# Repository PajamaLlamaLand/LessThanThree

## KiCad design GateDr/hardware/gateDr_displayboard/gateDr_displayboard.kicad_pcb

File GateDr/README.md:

# Gate Dr. 

The Gate Doctor is a multi-functional logic, comparator, and gate manipulation module in the Eurorack synth format.

The module is based around extracting, combining, and further modulating gate signals from your Eurorack system. It can be a simple comparator, logic module, clock divider, probability generator, gate delay (plus plenty of other features/modulation options), or many combinations of those at once!

The module consists of 2 channels, each with 2 inputs and 2 outputs, and 2 global CV inputs that can be routed to almost any parameter in the module. Each input is fed into a comparator with adjustable threshold (or assign it to CV)- each pair of channel inputs are then fed to 2 different logic gates (including a 'Bypass' that will send the comparator result to the Output section below it). The results of the logic operations are then fed into the Output section where the signal can be fed through a variety of gate-centric utilities, such as a clock divider, probability mask, gate delay, and more. 

As you can probably see already (and please read the manual in /GateDr/documentation/ to see all the other features it has!), the Gate Dr. is a very flexible utility tool designed to be able to create, combine, and fine-tune gate signals to send out to the rest of your Eurorack system. Whether you are extracting gates from LFOs, combining multiple gate sequencers and probability to create new generative sequences, or simply trimming a gate signal's length to make it play well with a module that wants short triggers, you may not need every feature it has on a given patch but it can find a place in nearly every patch you make <3

The Gate Doctor is currently [available for sale here.](https://www.tindie.com/products/41107/)

NOTE: The Gate Dr. is designed for control signals, not audio rate signals. However, you are highly encouraged to abuse this fact to create some unique glitchy digital textures.

# Feature List

Each channel in the Gate Dr. contains:

>   2 comparators with adjustable threshold, hysteresis, and ability to invert the signal.

>   2 separate logical operations on the 2 inputs, including combinational logic (AND, NAND, OR, NOR, XOR, XNOR), sequential logic (S-R latch, D-latch), and a BYPASS operation which ignores the 'operation' processing.

>   Output processing blocks that include various gate-related utilities, including a clock divider, a gate start-delay, a probability control, and a robust gate-to-trigger converter.

>   2 globally assignable CV signals, with CV control available for the vast majority of parameters.

The Gate Dr. also has the following features:

>   OLED screen, pushbutton encoder, and two Channel buttons for easy access to any parameter. 

>   Simple, easy to understand menu interface with shortcuts to menus on the panel. 

>   Automatic saving of all settings parameters. 

>   Reverse power protection. 

>   Super slim skiff-friendly design. 

>   USB-Micro Type B connection for easy drag-and-drop firmware updates. 

## Repo info

This repository contains the hardware design files and firmware for the Gate Dr. module, as well as associated documentation (manual, licenses, BOM, etc.).

## Build info

This firmware was built using Microchip Studio, and contains all relevant source files, third party dependencies, and associated Microchip Studio files for compilation. The repository also contains .uf2 files for uploading directly to the module. 

The hardware was designed using KiCad and the repository contains all relevant KiCad files for the main board, OLED display board, and front panel.

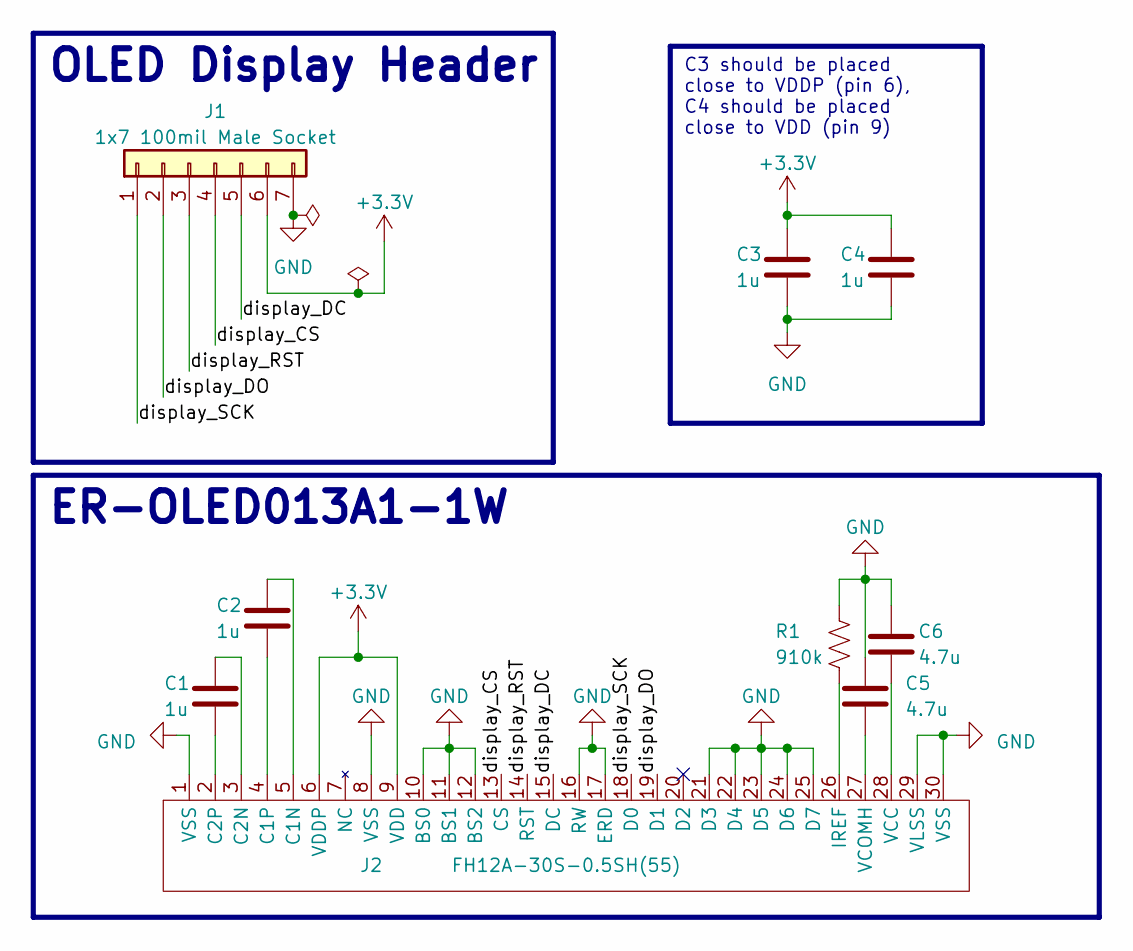
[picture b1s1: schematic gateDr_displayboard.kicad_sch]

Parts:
C1, C2, C3, C4: 1u; C_0603_1608Metric; Mouser Part No. GCM188R71E105KA64D
C5, C6: 4.7u; C_0603_1608Metric; Mouser Part No. GRM188Z71C475KE21D
J1: 1x7 100mil Male Socket; PinHeader_1x07_P2.54mm_Vertical
J2: FH12A-30S-0.5SH(55); FH12A-30S-0.5SH
R1: 910k; R_0402_1005Metric; Mouser Part No. CRCW0402910KFKED

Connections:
+3.3V: C3.1, C4.1, J1.6, J2.6 (VDDP), J2.9 (VDD)
/display_CS: J1.4, J2.13 (CS)
/display_DC: J1.5, J2.15 (DC)
/display_DO: J1.2, J2.19 (D1)
/display_RST: J1.3, J2.14 (RST)
/display_SCK: J1.1, J2.18 (D0)
GND: C3.2, C4.2, C5.1, C6.1, J1.7, J2.1 (VSS), J2.8 (VSS), J2.10 (BS0), J2.11 (BS1), J2.12 (BS2), J2.16 (RW), J2.17 (ERD), J2.21 (D3), J2.22 (D4), J2.23 (D5), J2.24 (D6), J2.25 (D7), J2.29 (VLSS), J2.30 (VSS), R1.1
unnamed: C2.1, J2.5 (C1N)
unnamed: C2.2, J2.4 (C1P)
unnamed: C1.1, J2.3 (C2N)
unnamed: C1.2, J2.2 (C2P)
unnamed: J2.26 (IREF), R1.2
unnamed: C6.2, J2.28 (VCC)
unnamed: C5.2, J2.27 (VCOMH)

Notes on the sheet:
ER-OLED013A1-1W
C3 should be placed close to VDDP (pin 6), C4 should be placed close to VDD (pin 9)
OLED Display Header

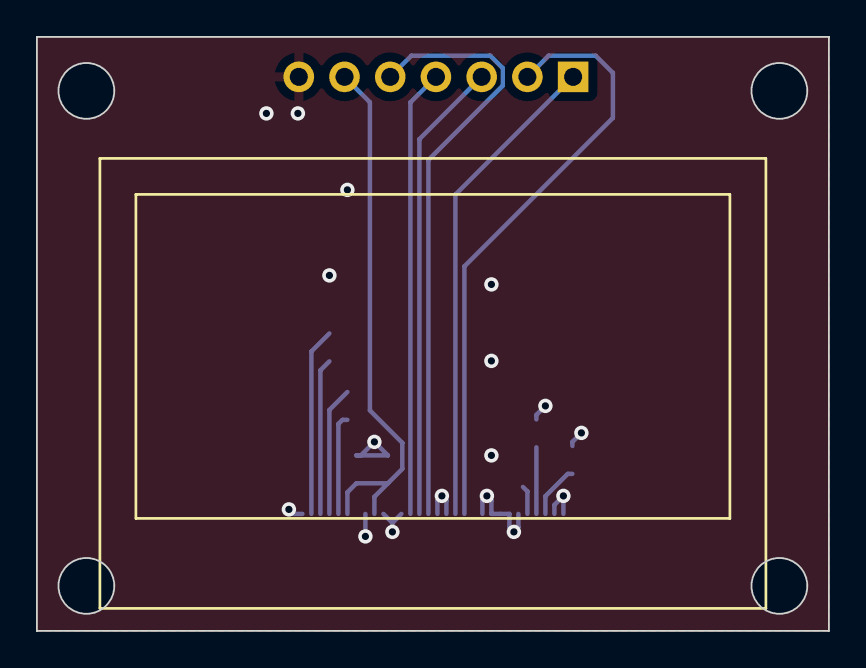
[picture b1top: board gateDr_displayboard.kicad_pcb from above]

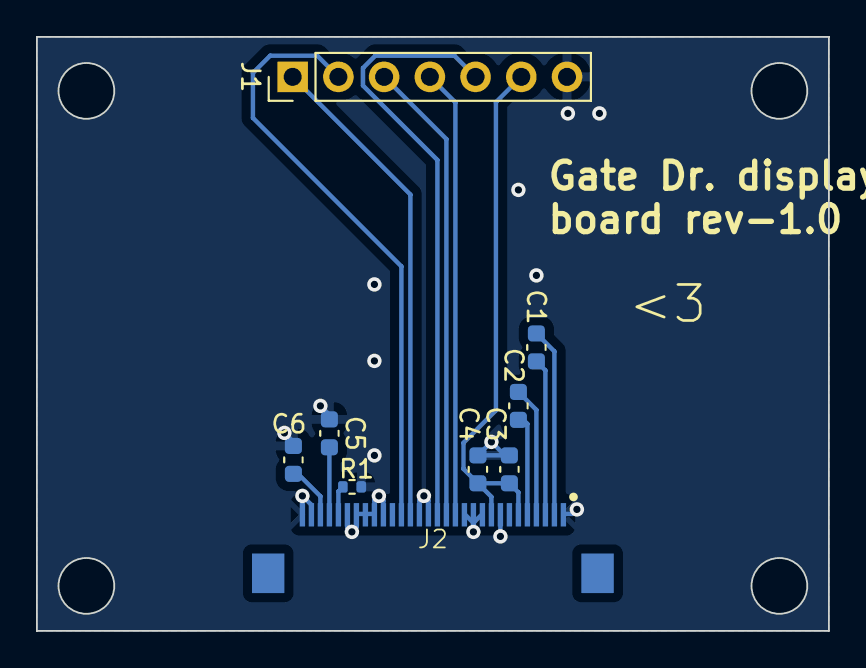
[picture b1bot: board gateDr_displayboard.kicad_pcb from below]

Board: 2 copper layers, 44.0 x 33.0 mm, 9 parts (9 on the bottom side), 14 nets.

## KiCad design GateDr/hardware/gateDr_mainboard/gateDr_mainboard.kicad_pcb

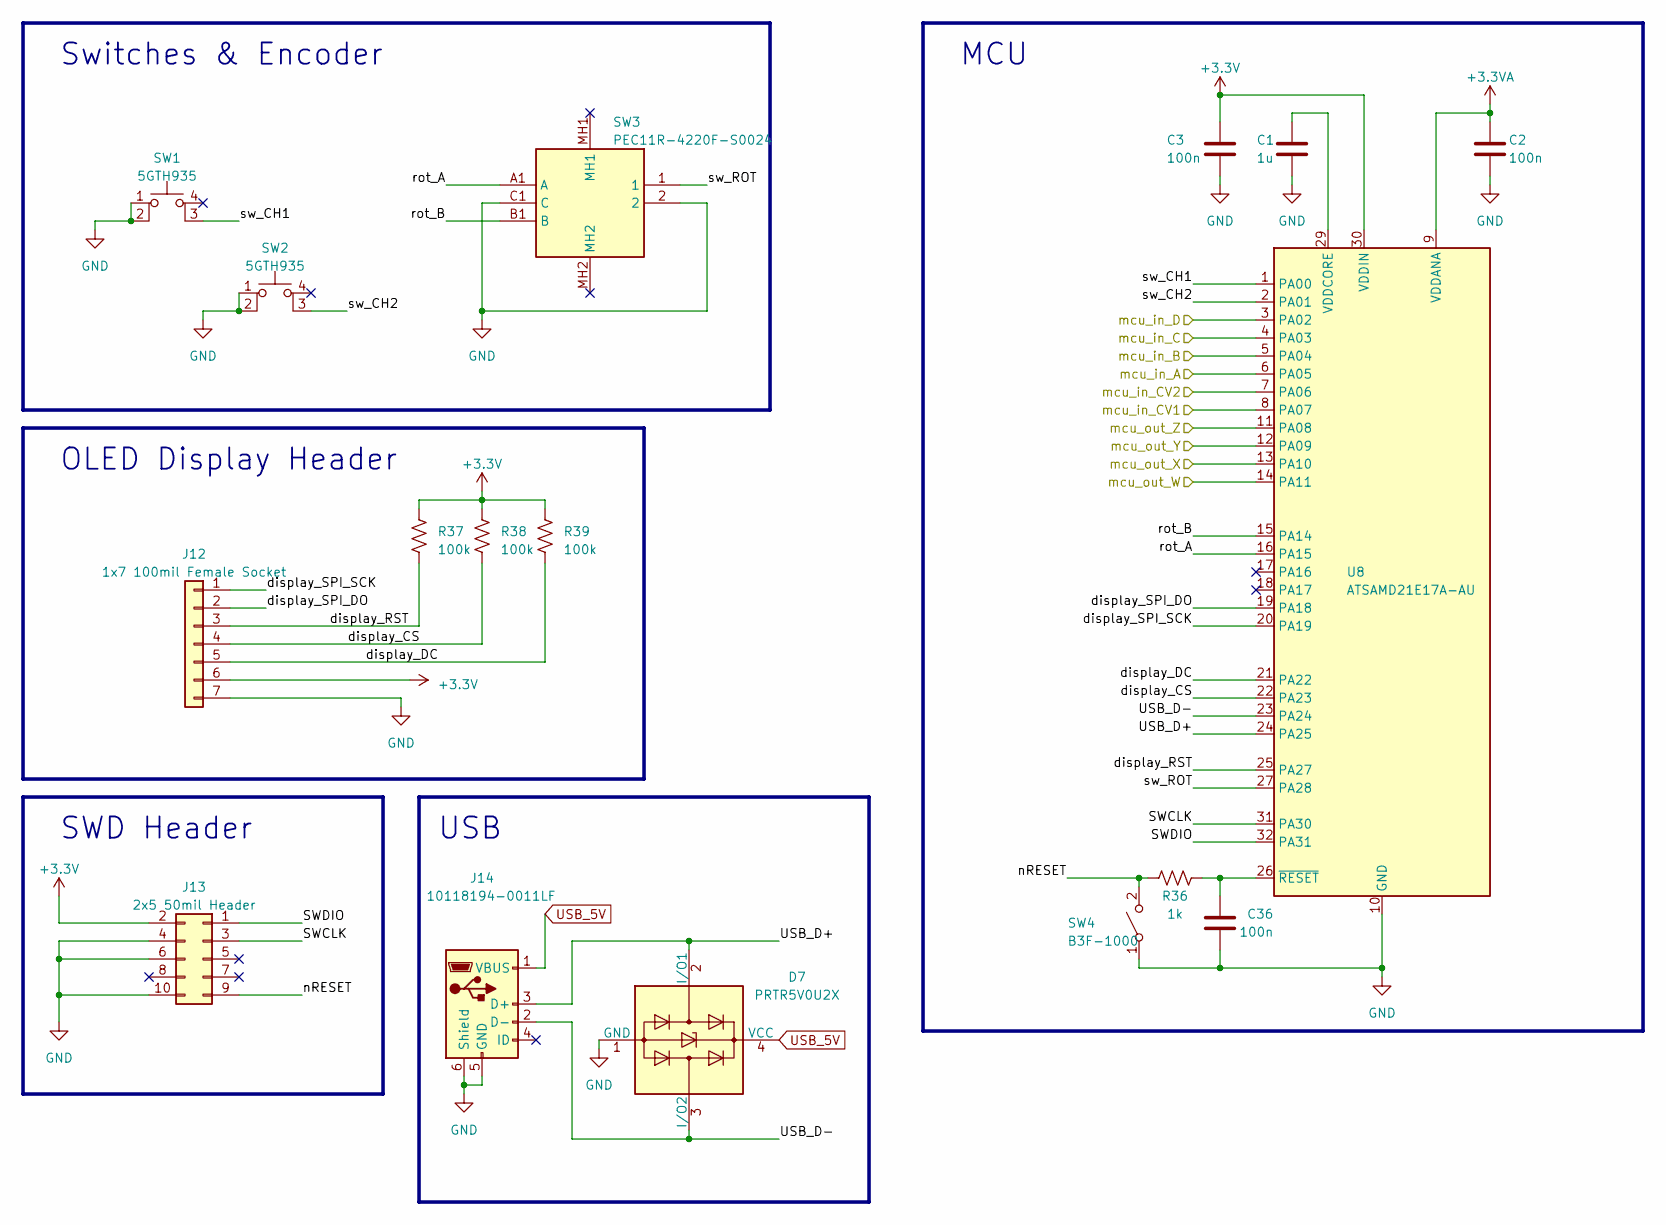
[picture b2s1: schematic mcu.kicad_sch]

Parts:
C1: 1u; C_0603_1608Metric; Mouser Part No. GCM188R71E105KA64D
C2, C3, C36: 100n; C_0402_1005Metric; Mouser Part No. GRM155R71H104KE14J
D7: PRTR5V0U2X; SOT-143; Mouser Part No. 771-PRTR5V0U2X-T/R
J12: 1x7 100mil Female Socket; PinSocket_1x07_P2.54mm_Vertical
J13: 2x5 50mil Header; PinSocket_2x05_P1.27mm_Vertical
J14: 10118194-0011LF; USB_Micro-B_Amphenol_10118194_Horizontal; Mouser Part No. 649-10118194-0011LF
R36: 1k; R_0402_1005Metric; Mouser Part No. CRCW04021K00FKED
R37, R38, R39: 100k; R_0402_1005Metric; Mouser Part No. CRCW0402100KFKED
SW1, SW2: 5GTH935
SW3: PEC11R-4220F-S0024; PEC11R4220FS0024; Mouser Part Number 652-PEC11R-4220F-S24
SW4: B3F-1000; SW_PUSH_6mm_H4.3mm
U8: ATSAMD21E17A-AU; TQFP-32_7x7mm_P0.8mm

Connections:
+3.3V: C3.1, J12.6, J13.2, R37.1, R38.1, R39.1, U8.30 (VDDIN); also elsewhere on the board
+3.3VA: C2.1, U8.9 (VDDANA); also elsewhere on the board
/Inputs/in_A: U8.6 (PA05); also elsewhere on the board
/Inputs/in_B: U8.5 (PA04); also elsewhere on the board
/Inputs/in_C: U8.4 (PA03); also elsewhere on the board
/Inputs/in_CV1: U8.8 (PA07); also elsewhere on the board
/Inputs/in_CV2: U8.7 (PA06); also elsewhere on the board
/Inputs/in_D: U8.3 (PA02); also elsewhere on the board
/MCU/SWCLK: J13.3, U8.31 (PA30)
/MCU/SWDIO: J13.1, U8.32 (PA31)
/MCU/USB_D+: D7.2 (I/O1), J14.3 (D+), U8.24 (PA25)
/MCU/USB_D-: D7.3 (I/O2), J14.2 (D-), U8.23 (PA24)
/MCU/display_CS: J12.4, R38.2, U8.22 (PA23)
/MCU/display_DC: J12.5, R39.2, U8.21 (PA22)
/MCU/display_RST: J12.3, R37.2, U8.25 (PA27)
/MCU/display_SPI_DO: J12.2, U8.19 (PA18)
/MCU/display_SPI_SCK: J12.1, U8.20 (PA19)
/MCU/mcu_out_W: U8.14 (PA11); also elsewhere on the board
/MCU/mcu_out_X: U8.13 (PA10); also elsewhere on the board
/MCU/mcu_out_Y: U8.12 (PA09); also elsewhere on the board
/MCU/mcu_out_Z: U8.11 (PA08); also elsewhere on the board
/MCU/nRESET: J13.9, R36.1, SW4.2 (B)
/MCU/rot_A: SW3.A1 (A), U8.16 (PA15)
/MCU/rot_B: SW3.B1 (B), U8.15 (PA14)
/MCU/sw_CH1: SW1.3 (K), U8.1 (PA00)
/MCU/sw_CH2: SW2.3 (K), U8.2 (PA01)
/MCU/sw_ROT: SW3.1, U8.27 (PA28)
GND: C1.2, C2.2, C3.2, C36.2, D7.1 (GND), J12.7, J13.4, J13.6, J13.10, J14.5 (GND), J14.6 (Shield), SW1.1, SW1.2, SW2.1, SW2.2, SW3.2, SW3.C1 (C), SW4.1 (A), U8.10 (GND), U8.28 (GND); also elsewhere on the board
unnamed: C1.1, U8.29 (VDDCORE)
unnamed: C36.1, R36.2, U8.26 (~RESET)
USB_5V: D7.4 (VCC), J14.1 (VBUS); also elsewhere on the board

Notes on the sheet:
Switches & Encoder
SWD Header
USB
OLED Display Header
MCU

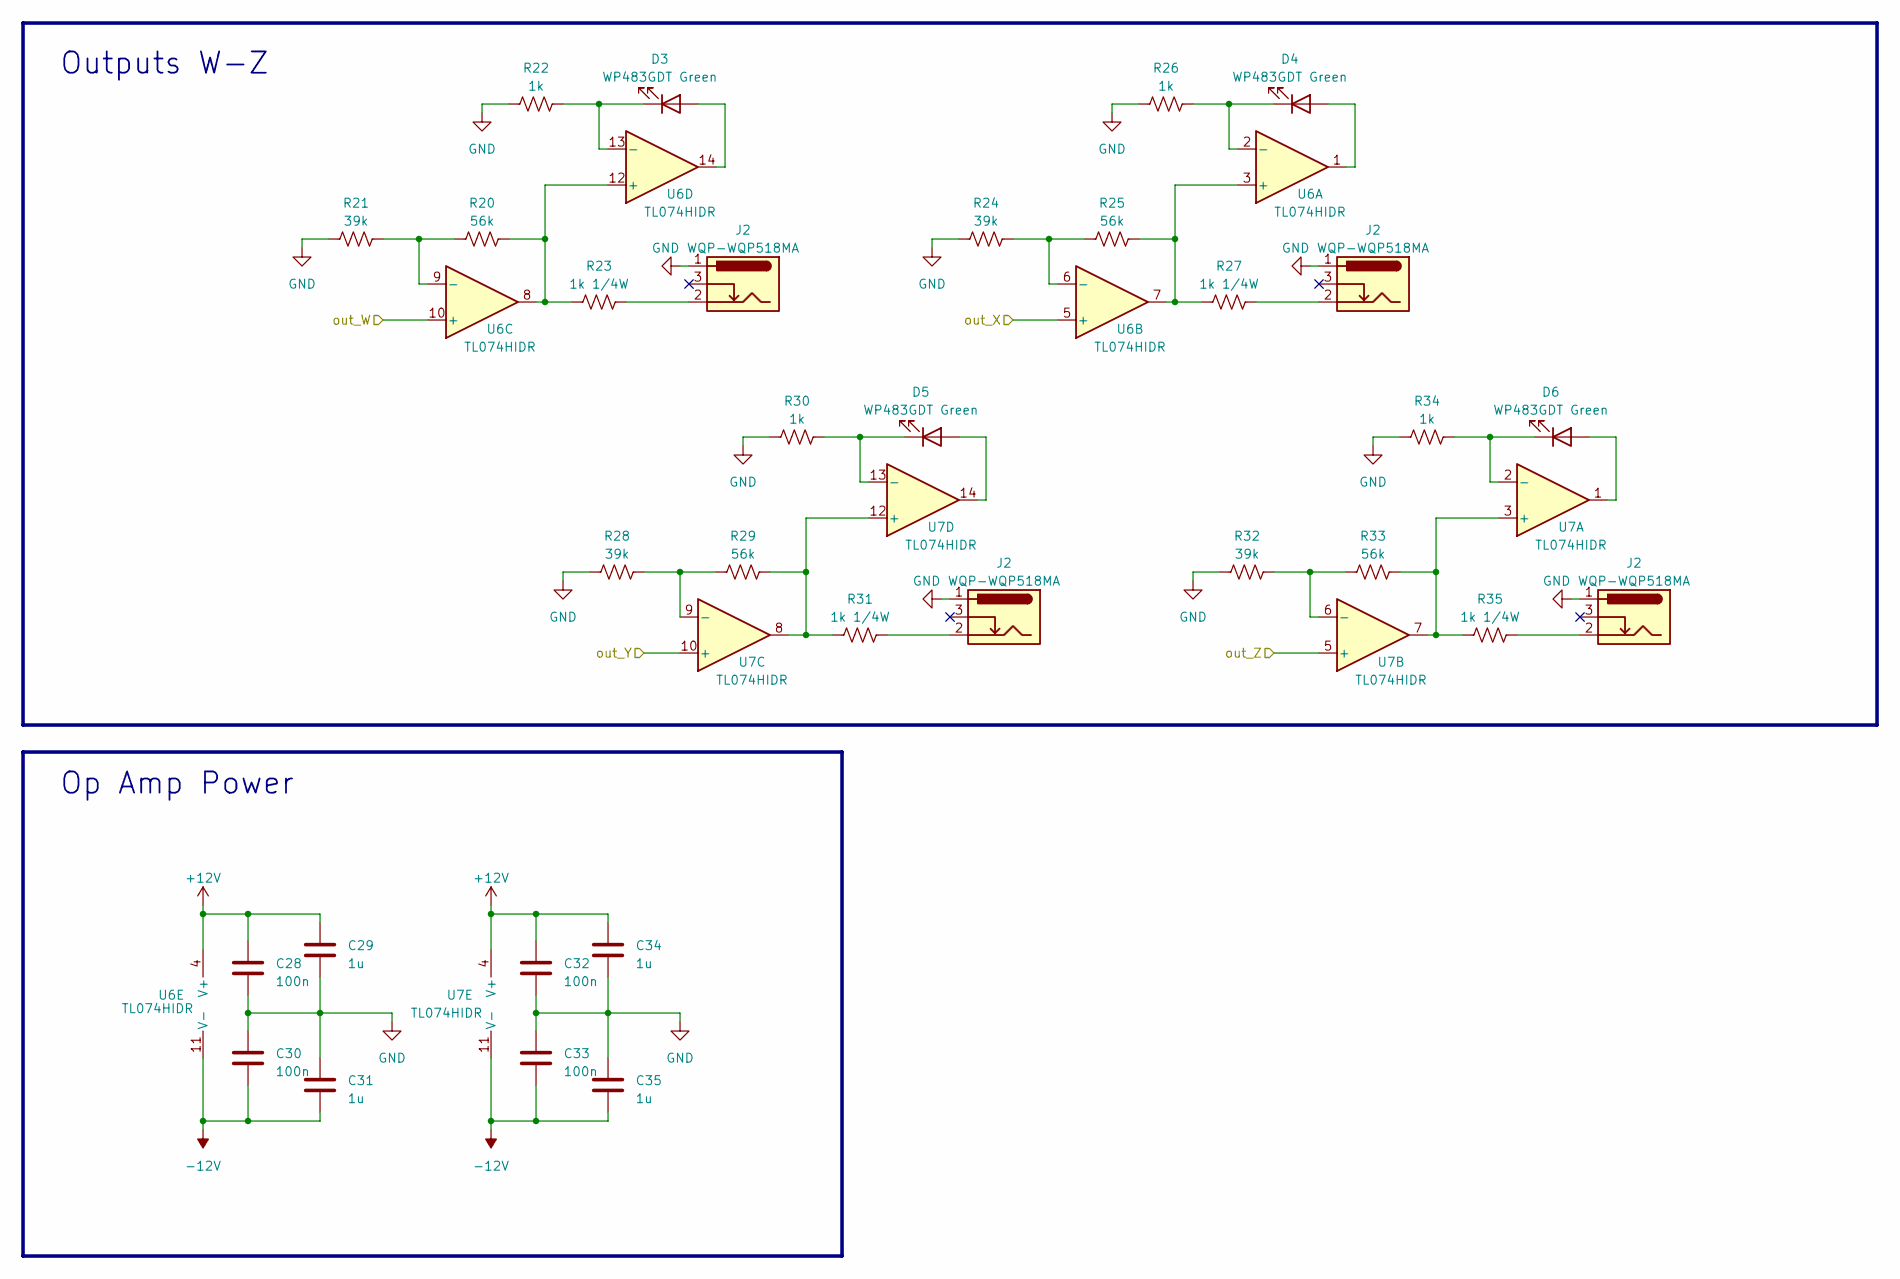
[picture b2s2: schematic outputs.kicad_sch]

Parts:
C28, C30, C32, C33: 100n; C_0402_1005Metric; Mouser Part No. GRM155R71H104KE14J
C29, C31, C34, C35: 1u; C_0603_1608Metric; Mouser Part No. GCM188R71E105KA64D
D3, D4, D5, D6: WP483GDT Green; LED_D5.0mm_FlatTop
J2: WQP-WQP518MA; AudioJack_WQP518MA
R20, R25, R29, R33: 56k; R_0402_1005Metric; Mouser Part No. CRCW040256K0FKED
R21, R24, R28, R32: 39k; R_0402_1005Metric; Mouser Part No. CRCW040239K0FKED
R22, R26, R30, R34: 1k; R_0402_1005Metric; Mouser Part No. CRCW04021K00FKED
R23, R27, R31, R35: 1k 1/4W; R_0805_2012Metric; Mouser Part No. RCC08051K00FKEA
U6, U7: TL074HIDR; SOIC-14_3.9x8.7mm_P1.27mm

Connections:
+12V: C28.1, C29.1, C32.1, C34.1, U6.4 (V+), U7.4 (V+); also elsewhere on the board
-12V: C30.2, C31.2, C33.2, C35.2, U6.11 (V-), U7.11 (V-); also elsewhere on the board
/MCU/mcu_out_W: U6.10 (+); also elsewhere on the board
/MCU/mcu_out_X: U6.5 (+); also elsewhere on the board
/MCU/mcu_out_Y: U7.10 (+); also elsewhere on the board
/MCU/mcu_out_Z: U7.5 (+); also elsewhere on the board
GND: C28.2, C29.2, C30.1, C31.1, C32.2, C33.1, C34.2, C35.1, J2.1, J2.3, R21.1, R22.1, R24.1, R26.1, R28.1, R30.1, R32.1, R34.1; also elsewhere on the board
unnamed: D3.2 (A), U6.14
unnamed: D3.1 (K), R22.2, U6.13 (-)
unnamed: D4.2 (A), U6.1
unnamed: D4.1 (K), R26.2, U6.2 (-)
unnamed: D5.2 (A), U7.14
unnamed: D5.1 (K), R30.2, U7.13 (-)
unnamed: D6.2 (A), U7.1
unnamed: D6.1 (K), R34.2, U7.2 (-)
unnamed: R25.2, R27.1, U6.3 (+), U6.7
unnamed: R24.2, R25.1, U6.6 (-)
unnamed: R20.1, R21.2, U6.9 (-)
unnamed: R20.2, R23.1, U6.8, U6.12 (+)
unnamed: R33.2, R35.1, U7.3 (+), U7.7
unnamed: R32.2, R33.1, U7.6 (-)
unnamed: R28.2, R29.1, U7.9 (-)
unnamed: R29.2, R31.1, U7.8, U7.12 (+)

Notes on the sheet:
Op Amp Power
Outputs W-Z

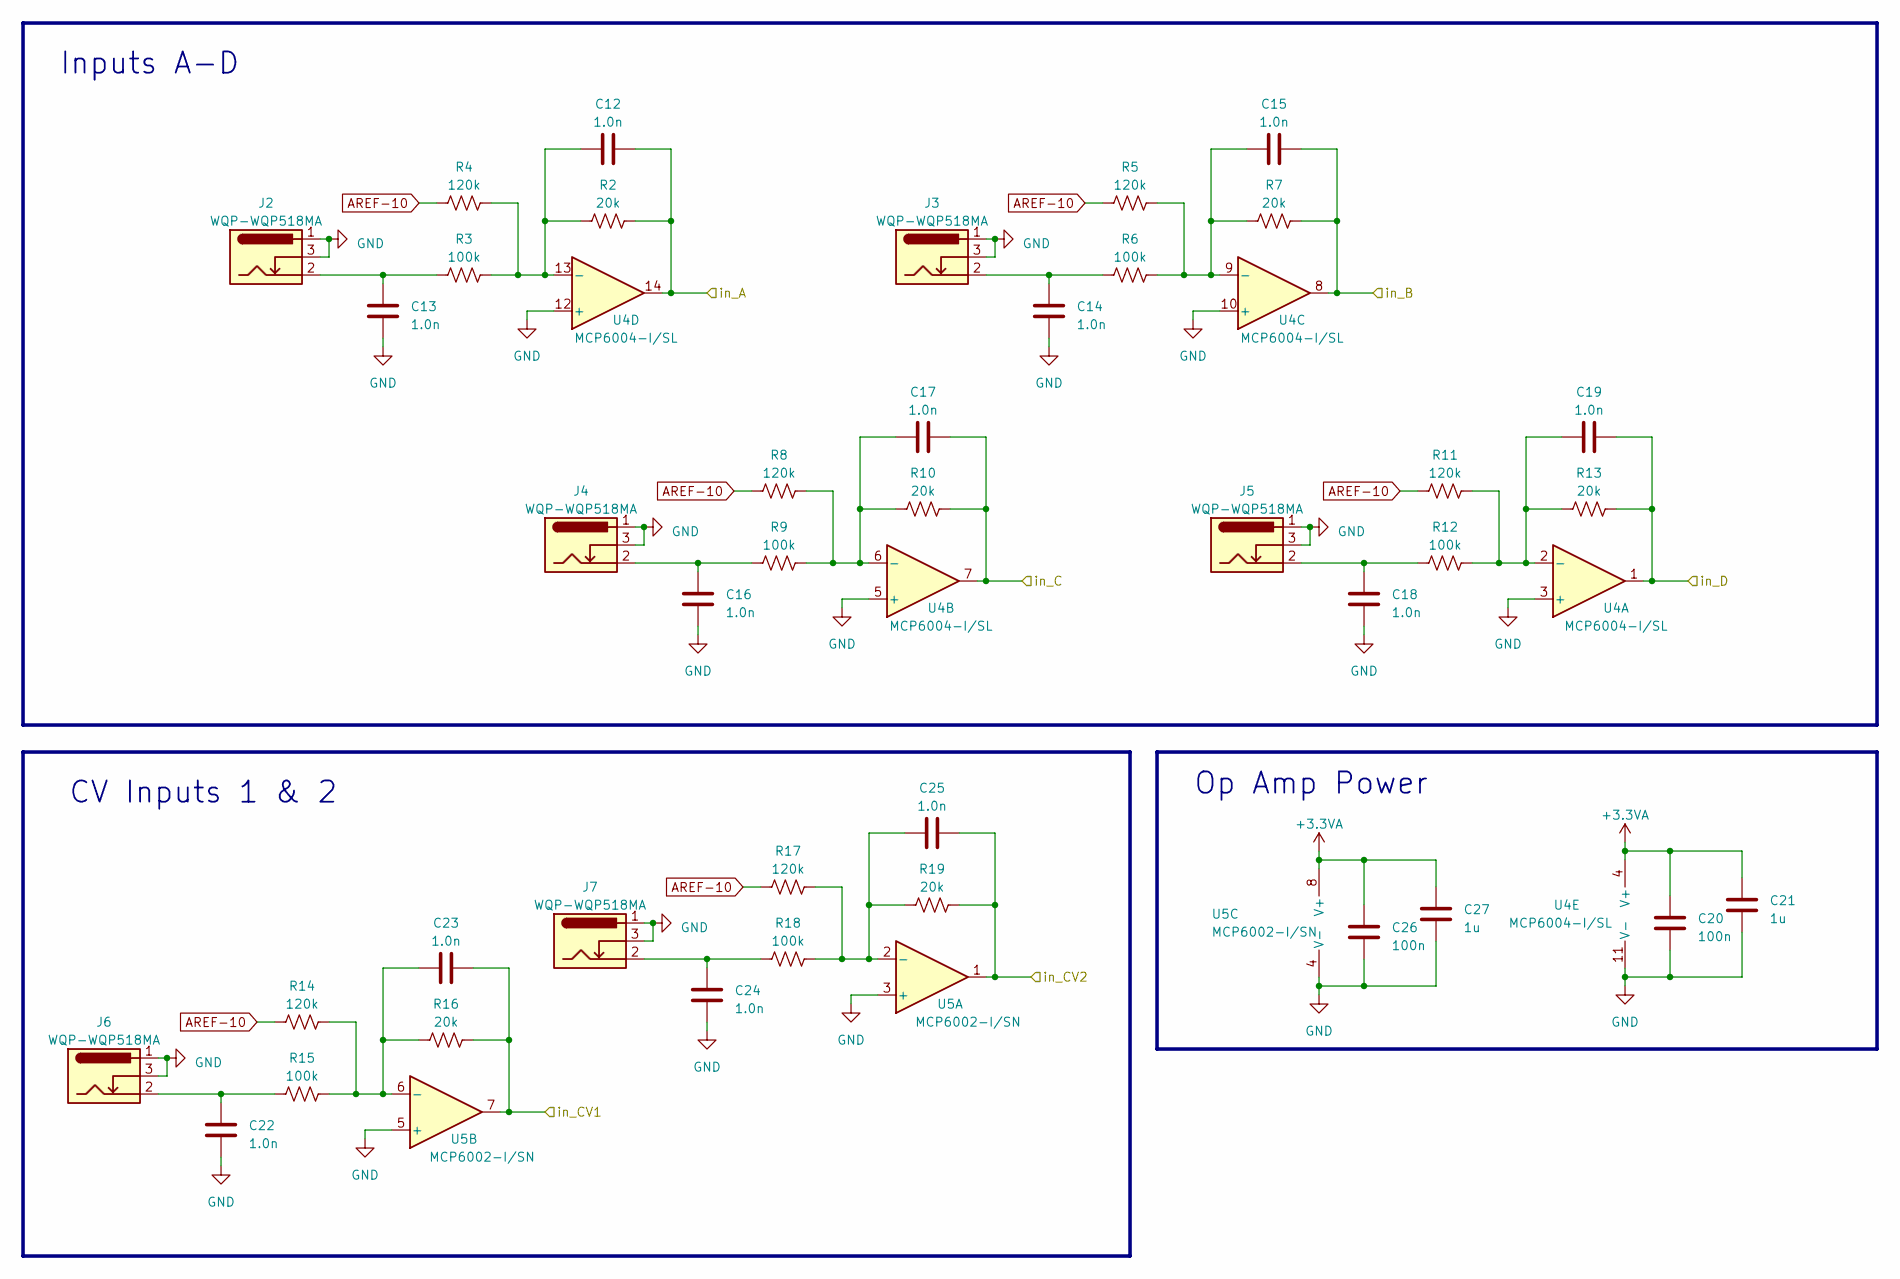
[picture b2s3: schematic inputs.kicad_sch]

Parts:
C12, C13, C14, C15, C16, C17, C18, C19, C22, C23, C24, C25: 1.0n; C_0402_1005Metric; Mouser Part No. GRM155R71H102KA01J
C20, C26: 100n; C_0402_1005Metric; Mouser Part No. GRM155R71H104KE14J
C21, C27: 1u; C_0603_1608Metric; Mouser Part No. GCM188R71E105KA64D
J2, J3, J4, J5, J6, J7: WQP-WQP518MA; AudioJack_WQP518MA
R2, R7, R10, R13, R16, R19: 20k; R_0402_1005Metric; Mouser Part No. CRCW040220K0FKED
R3, R6, R9, R12, R15, R18: 100k; R_0402_1005Metric; Mouser Part No. CRCW0402100KFKED
R4, R5, R8, R11, R14, R17: 120k; R_0402_1005Metric; Mouser Part No. CRCW0402120KFKED
U4: MCP6004-I/SL; SOIC-14_3.9x8.7mm_P1.27mm
U5: MCP6002-I/SN; SOIC-8_3.9x4.9mm_P1.27mm

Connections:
+3.3VA: C20.1, C21.1, C26.1, C27.1, U4.4 (V+), U5.8 (V+); also elsewhere on the board
/Inputs/in_A: C12.2, R2.2, U4.14; also elsewhere on the board
/Inputs/in_B: C15.2, R7.2, U4.8; also elsewhere on the board
/Inputs/in_C: C17.2, R10.2, U4.7; also elsewhere on the board
/Inputs/in_CV1: C23.2, R16.2, U5.7; also elsewhere on the board
/Inputs/in_CV2: C25.2, R19.2, U5.1; also elsewhere on the board
/Inputs/in_D: C19.2, R13.2, U4.1; also elsewhere on the board
AREF-10: R4.1, R5.1, R8.1, R11.1, R14.1, R17.1; also elsewhere on the board
GND: C13.2, C14.2, C16.2, C18.2, C20.2, C21.2, C22.2, C24.2, C26.2, C27.2, J2.1, J2.3, J3.1, J3.3, J4.1, J4.3, J5.1, J5.3, J6.1, J6.3, J7.1, J7.3, U4.3 (+), U4.5 (+), U4.10 (+), U4.11 (V-), U4.12 (+), U5.3 (+), U5.4 (V-), U5.5 (+); also elsewhere on the board
unnamed: C14.1, J3.2, R6.1
unnamed: C16.1, J4.2, R9.1
unnamed: C18.1, J5.2, R12.1
unnamed: C22.1, J6.2, R15.1
unnamed: C24.1, J7.2, R18.1
unnamed: C19.1, R11.2, R12.2, R13.1, U4.2 (-)
unnamed: C17.1, R8.2, R9.2, R10.1, U4.6 (-)
unnamed: C15.1, R5.2, R6.2, R7.1, U4.9 (-)
unnamed: C12.1, R2.1, R3.2, R4.2, U4.13 (-)
unnamed: C25.1, R17.2, R18.2, R19.1, U5.2 (-)
unnamed: C23.1, R14.2, R15.2, R16.1, U5.6 (-)

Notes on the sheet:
Inputs A-D
CV Inputs 1 & 2
Op Amp Power

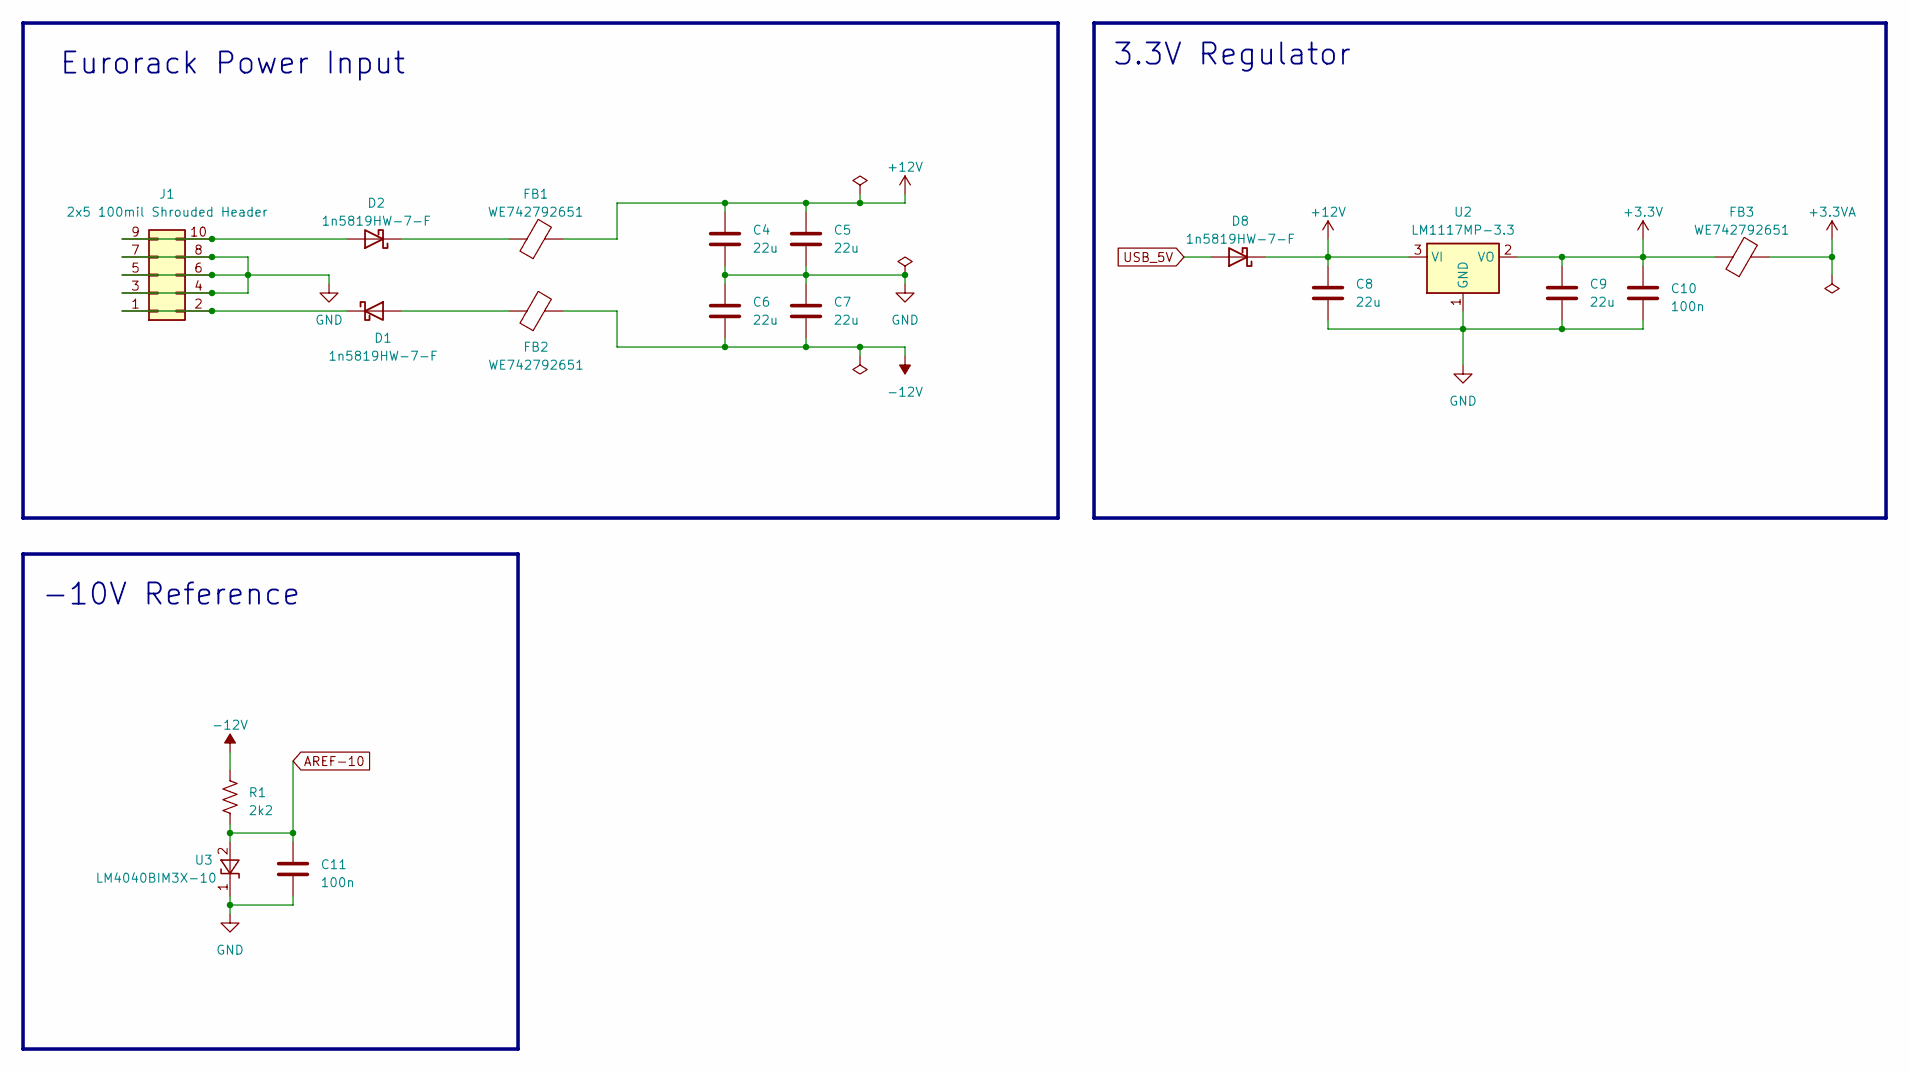
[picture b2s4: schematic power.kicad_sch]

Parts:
C4, C5, C6, C7, C8, C9: 22u; C_0805_2012Metric; Mouser Part No. CL21A226MAYNNNE
C10, C11: 100n; C_0402_1005Metric; Mouser Part No. GRM155R71H104KE14J
D1, D2, D8: 1n5819HW-7-F; D_SOD-123
FB1, FB2, FB3: WE742792651; BEADC1608X100N
J1: 2x5 100mil Shrouded Header; IDC-Header_2x05_P2.54mm_Vertical
R1: 2k2; R_0402_1005Metric; Mouser Part No. CRCW04022K20FKED
U2: LM1117MP-3.3; SOT-223-3_TabPin2
U3: LM4040BIM3X-10; SOT-23

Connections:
+3.3V: C9.1, C10.1, FB3.1, U2.2 (VO); also elsewhere on the board
+3.3VA: FB3.2; also elsewhere on the board
+12V: C4.1, C5.1, C8.1, D8.1 (K), FB1.2, U2.3 (VI); also elsewhere on the board
-12V: C6.2, C7.2, FB2.2, R1.1; also elsewhere on the board
AREF-10: C11.1, R1.2, U3.2 (A); also elsewhere on the board
GND: C4.2, C5.2, C6.1, C7.1, C8.2, C9.2, C10.2, C11.2, J1.3, J1.4, J1.5, J1.6, J1.7, J1.8, U2.1 (GND), U3.1 (K); also elsewhere on the board
unnamed: D1.2 (A), FB2.1
unnamed: D1.1 (K), J1.1, J1.2
unnamed: D2.2 (A), J1.9, J1.10
unnamed: D2.1 (K), FB1.1
USB_5V: D8.2 (A); also elsewhere on the board

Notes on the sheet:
-10V Reference
3.3V Regulator
Eurorack Power Input

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
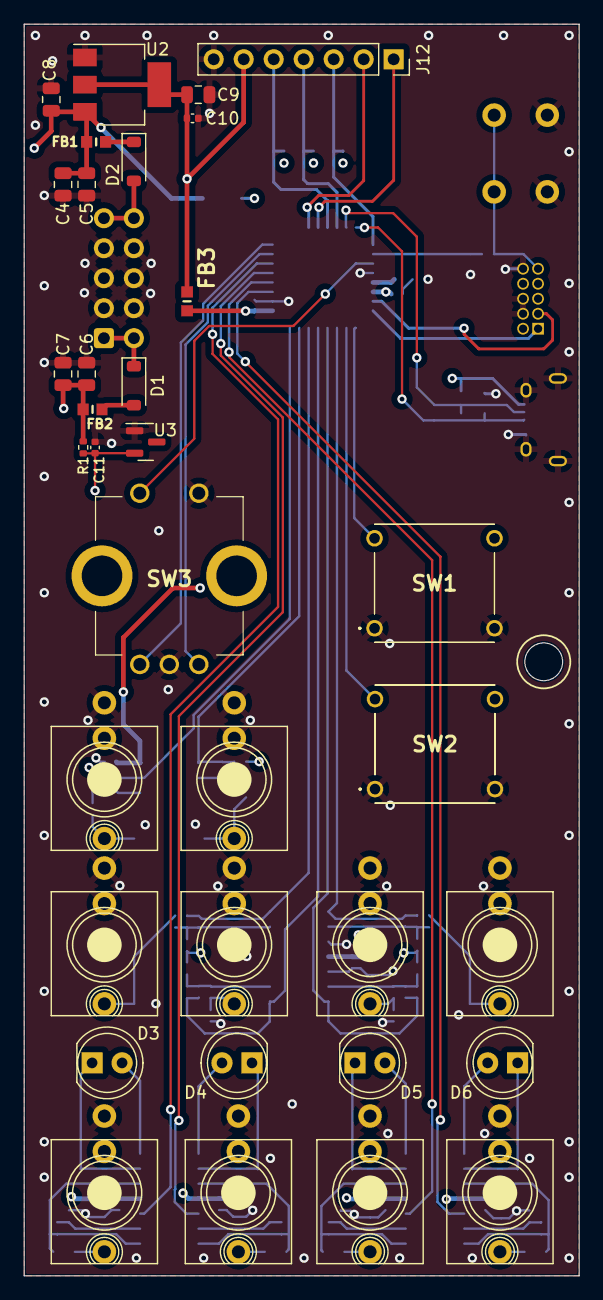
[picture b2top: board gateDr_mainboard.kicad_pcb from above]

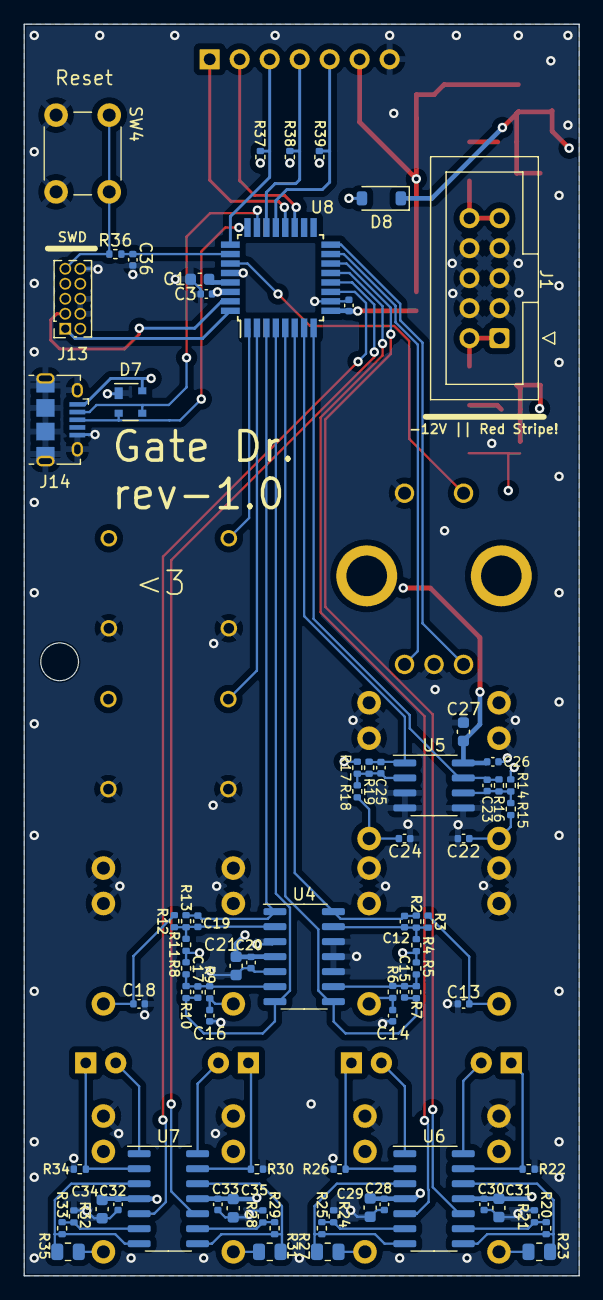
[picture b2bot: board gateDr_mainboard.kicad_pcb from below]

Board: 4 copper layers, 47.0 x 106.0 mm, 111 parts (77 on the bottom side), 70 nets.

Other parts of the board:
J8, J9, J10, J11: WQP-WQP518MA; AudioJack_WQP518MA

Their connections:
GND: J8.1, J9.1, J10.1, J11.1; also elsewhere on the board

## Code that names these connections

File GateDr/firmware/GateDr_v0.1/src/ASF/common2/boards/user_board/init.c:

/**
 * \file
 *
 * \brief User board initialization template
 *
 */
/*
 * Support and FAQ: visit <a href="https://www.microchip.com/support/">Microchip Support</a>
 */

#include <asf.h>
#include <board.h>
#include <conf_board.h>

#if defined(__GNUC__)
void board_init(void) WEAK __attribute__((alias("system_board_init")));
#elif defined(__ICCARM__)
void board_init(void);
#  pragma weak board_init=system_board_init
#endif

void system_board_init(void)
{
	/* This function is meant to contain board-specific initialization code
	 * for, e.g., the I/O pins. The initialization can rely on application-
	 * specific board configuration, found in conf_board.h.
	 */
	
	struct port_config pin_conf;
	port_get_config_defaults(&pin_conf);
	
	pin_conf.direction = PORT_PIN_DIR_OUTPUT;
	port_pin_set_config(PIN_PA11, &pin_conf);	// output W
	port_pin_set_output_level(PIN_PA11, false);
	port_pin_set_config(PIN_PA10, &pin_conf);	// output X
	port_pin_set_output_level(PIN_PA10, false);
	port_pin_set_config(PIN_PA09, &pin_conf);	// output Y
	port_pin_set_output_level(PIN_PA09, false);
	port_pin_set_config(PIN_PA08, &pin_conf);	// output Z
	port_pin_set_output_level(PIN_PA08, false);
	
	port_pin_set_config(PIN_PA18, &pin_conf);	// SPI/SSD1306 MOSI
	port_pin_set_config(PIN_PA19, &pin_conf);	// SPI/SSD1306 SCK
	
	pin_conf.direction = PORT_PIN_DIR_INPUT;

	// the following inputs are set up automatically during the configure_adc() 
	// function in main
// 	pin_conf.input_pull = PORT_PIN_PULL_NONE;
// 	port_pin_set_config(PIN_PA05, &pin_conf);	// input A
// 	port_pin_set_config(PIN_PA04, &pin_conf);	// input B
// 	port_pin_set_config(PIN_PA03, &pin_conf);	// input C
// 	port_pin_set_config(PIN_PA02, &pin_conf);	// input D
// 	port_pin_set_config(PIN_PA07, &pin_conf);	// CV input 1
// 	port_pin_set_config(PIN_PA06, &pin_conf);	// CV input 2

	pin_conf.input_pull = PORT_PIN_PULL_UP;
	
	port_pin_set_config(PIN_PA00, &pin_conf);	// pushbutton 1
	port_pin_set_config(PIN_PA01, &pin_conf);	// pushbutton 2
	port_pin_set_config(PIN_PA15, &pin_conf);	// encoder A
	port_pin_set_config(PIN_PA14, &pin_conf);	// encoder B
	port_pin_set_config(PIN_PA28, &pin_conf);	// encoder pushbutton
}

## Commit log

2025-09-24 Added front panel image to /documentation/ and linked in README.md
2025-09-25 updated README image reference
2025-09-25 resized front panel image for better git page presentation
2025-09-25 resized front panel image within README using HTML object
2025-12-18 Display legibility updates, uint16_t param bug fix
2026-03-04 added link to Tindie store page
2026-03-04 updated ssd1306 callback routine
